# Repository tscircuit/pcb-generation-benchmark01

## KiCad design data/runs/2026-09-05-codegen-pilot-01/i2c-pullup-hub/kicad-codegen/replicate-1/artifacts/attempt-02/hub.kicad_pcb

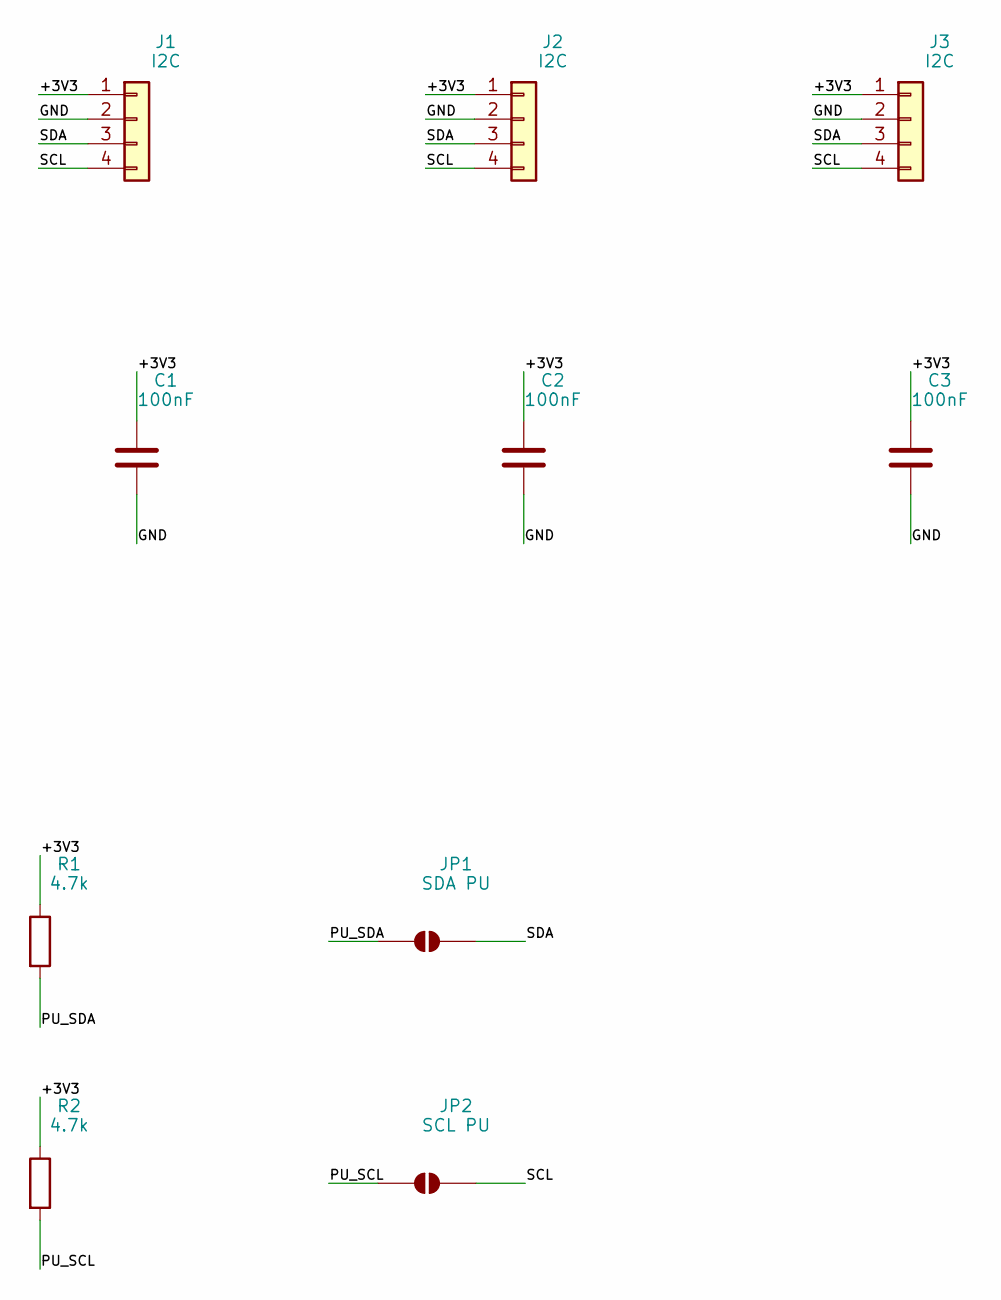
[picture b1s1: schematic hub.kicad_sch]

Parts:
C1, C2, C3: 100nF; C_0805_2012Metric
J1, J2, J3: I2C; PinHeader_1x04_P2.54mm_Vertical
JP1: SDA PU; SolderJumper-2_P1.3mm_Open_Pad1.0x1.5mm
JP2: SCL PU; SolderJumper-2_P1.3mm_Open_Pad1.0x1.5mm
R1, R2: 4.7k; R_0805_2012Metric

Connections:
/+3V3: C1.1, C2.1, C3.1, J1.1, J2.1, J3.1, R1.1, R2.1
/GND: C1.2, C2.2, C3.2, J1.2, J2.2, J3.2
/PU_SCL: JP2.1 (A), R2.2
/PU_SDA: JP1.1 (A), R1.2
/SCL: J1.4, J2.4, J3.4, JP2.2 (B)
/SDA: J1.3, J2.3, J3.3, JP1.2 (B)

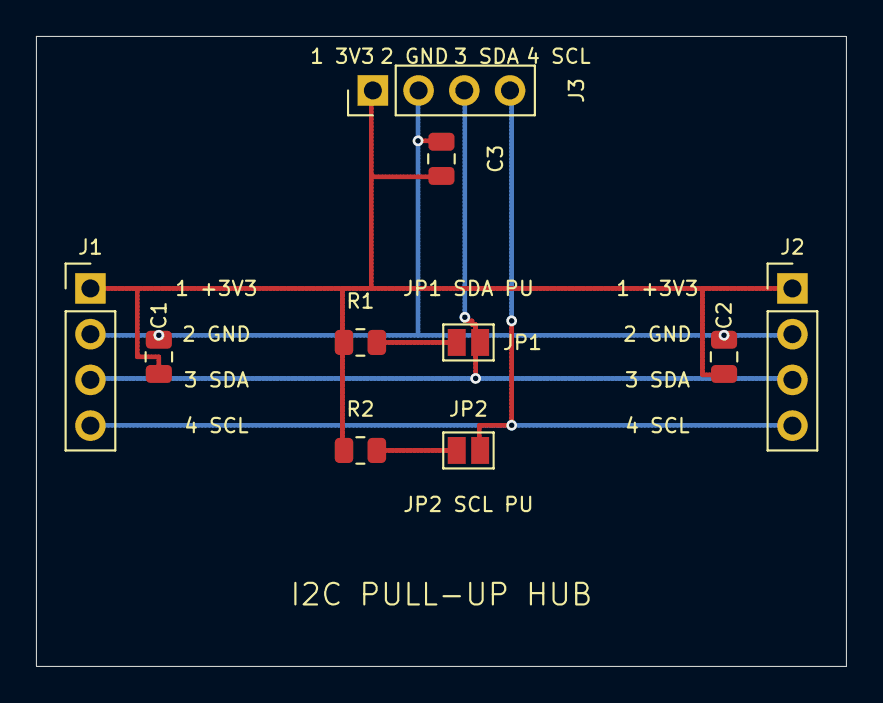
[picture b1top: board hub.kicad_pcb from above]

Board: 2 copper layers, 45.0 x 35.0 mm, 10 parts (0 on the bottom side), 6 nets.

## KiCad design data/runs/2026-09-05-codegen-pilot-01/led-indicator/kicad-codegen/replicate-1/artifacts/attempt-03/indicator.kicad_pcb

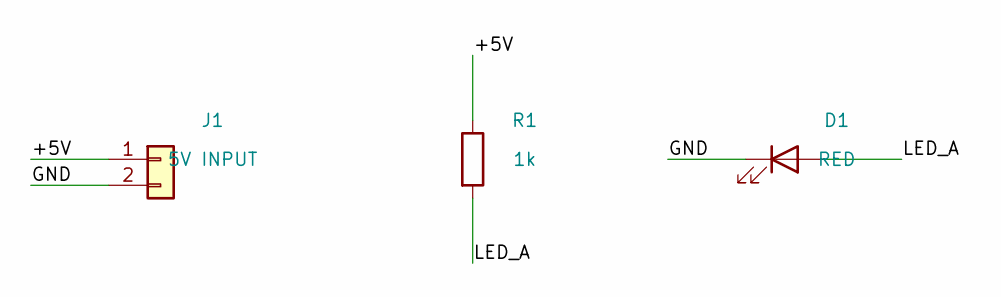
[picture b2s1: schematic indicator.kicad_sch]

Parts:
D1: RED; LED_0805_2012Metric
J1: 5V INPUT; PinHeader_1x02_P2.54mm_Vertical
R1: 1k; R_0805_2012Metric

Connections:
/+5V: J1.1, R1.1
/GND: D1.1 (K), J1.2
/LED_A: D1.2 (A), R1.2

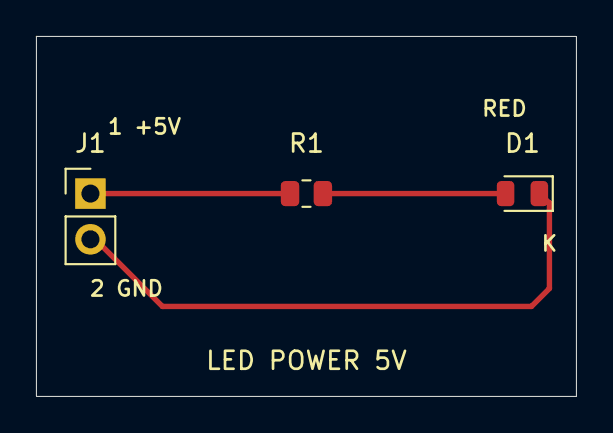
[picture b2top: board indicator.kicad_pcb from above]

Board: 2 copper layers, 30.0 x 20.0 mm, 3 parts (0 on the bottom side), 3 nets.

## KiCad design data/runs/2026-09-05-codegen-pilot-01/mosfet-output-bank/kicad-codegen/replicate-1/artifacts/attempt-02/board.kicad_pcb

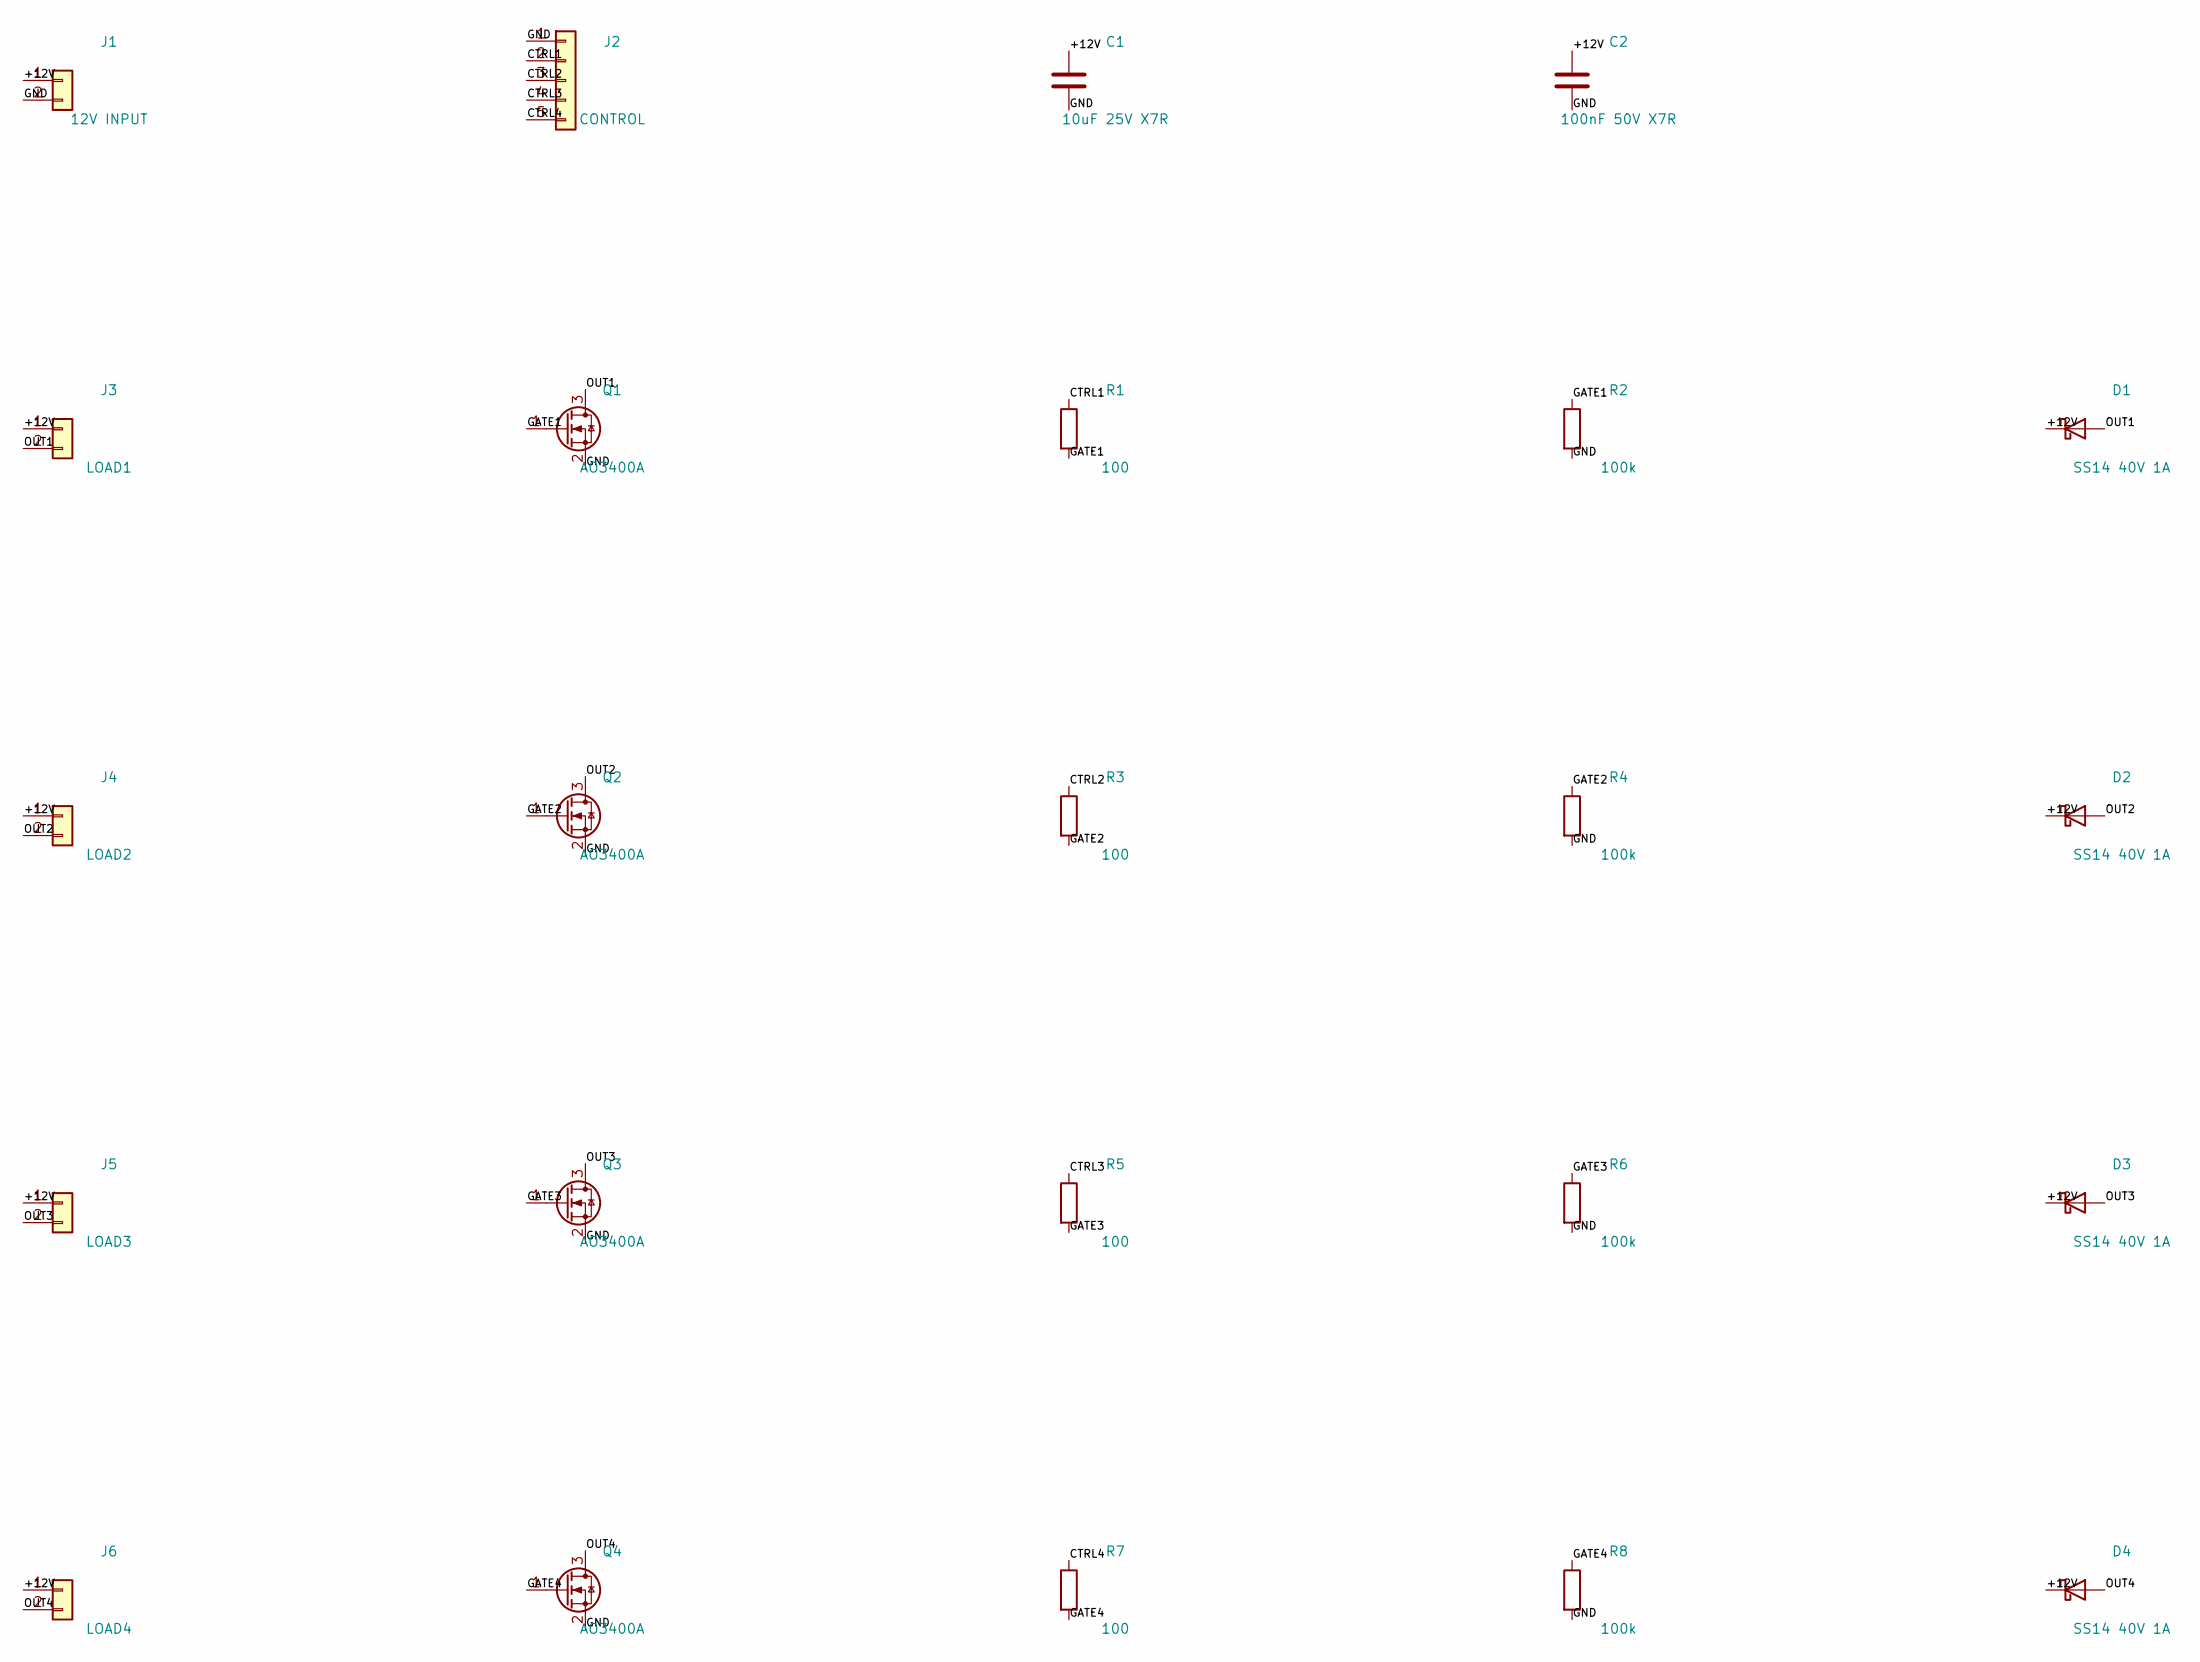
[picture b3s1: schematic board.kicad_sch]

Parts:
C1: 10uF 25V X7R; C_0805_2012Metric
C2: 100nF 50V X7R; C_0805_2012Metric
D1, D2, D3, D4: SS14 40V 1A; D_SMA
J1: 12V INPUT; PinHeader_1x02_P2.54mm_Vertical
J2: CONTROL; PinHeader_1x05_P2.54mm_Vertical
J3: LOAD1; PinHeader_1x02_P2.54mm_Vertical
J4: LOAD2; PinHeader_1x02_P2.54mm_Vertical
J5: LOAD3; PinHeader_1x02_P2.54mm_Vertical
J6: LOAD4; PinHeader_1x02_P2.54mm_Vertical
Q1, Q2, Q3, Q4: AO3400A; SOT-23
R1, R3, R5, R7: 100; R_0805_2012Metric
R2, R4, R6, R8: 100k; R_0805_2012Metric

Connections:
+12V: C1.1, C2.1, D1.1 (K), D2.1 (K), D3.1 (K), D4.1 (K), J1.1, J3.1, J4.1, J5.1, J6.1
CTRL1: J2.2, R1.1
CTRL2: J2.3, R3.1
CTRL3: J2.4, R5.1
CTRL4: J2.5, R7.1
GATE1: Q1.1 (G), R1.2, R2.1
GATE2: Q2.1 (G), R3.2, R4.1
GATE3: Q3.1 (G), R5.2, R6.1
GATE4: Q4.1 (G), R7.2, R8.1
GND: C1.2, C2.2, J1.2, J2.1, Q1.2 (S), Q2.2 (S), Q3.2 (S), Q4.2 (S), R2.2, R4.2, R6.2, R8.2
OUT1: D1.2 (A), J3.2, Q1.3 (D)
OUT2: D2.2 (A), J4.2, Q2.3 (D)
OUT3: D3.2 (A), J5.2, Q3.3 (D)
OUT4: D4.2 (A), J6.2, Q4.3 (D)

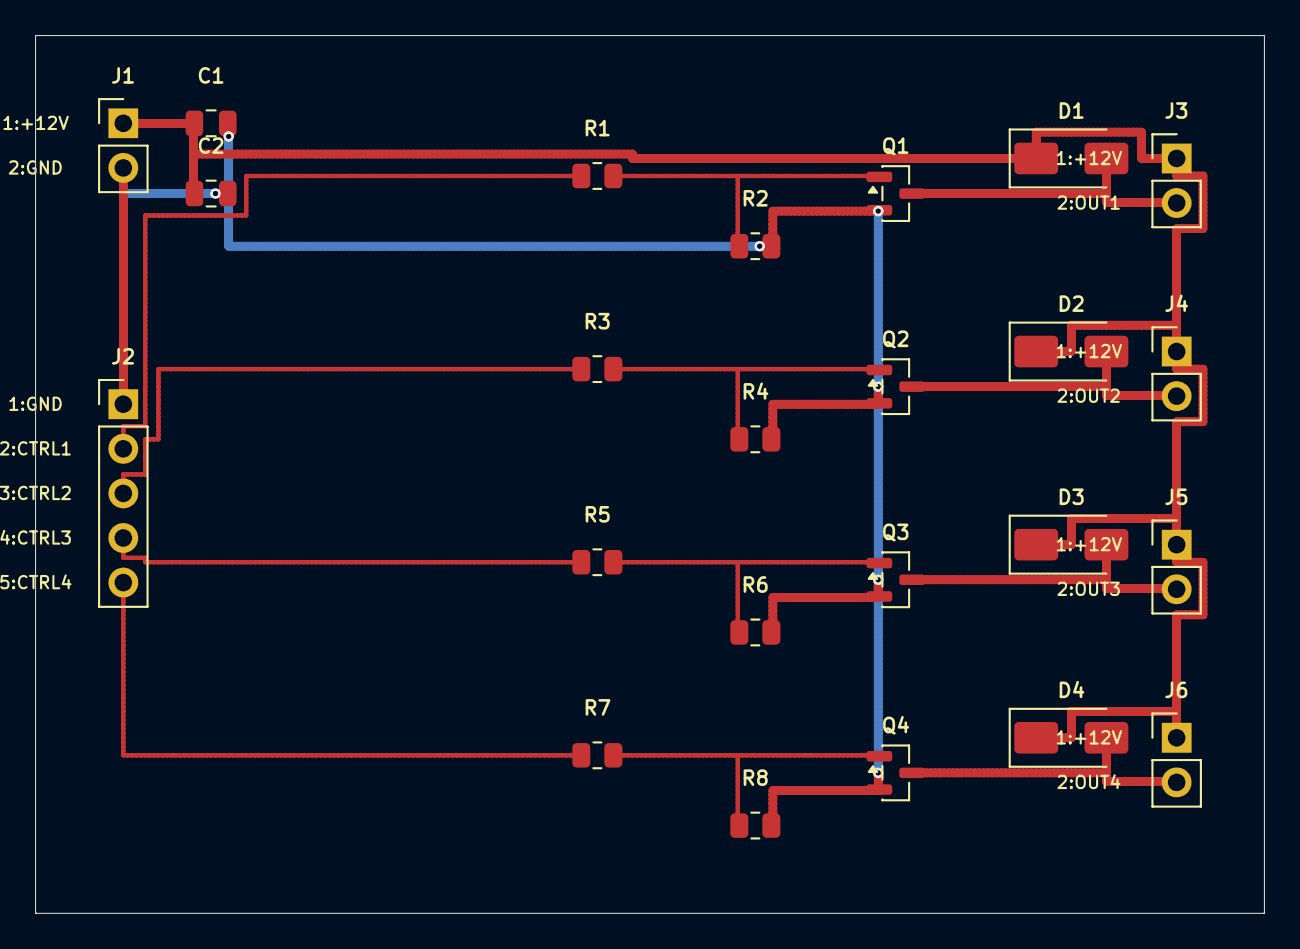
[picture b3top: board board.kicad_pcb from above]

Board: 2 copper layers, 70.0 x 50.0 mm, 24 parts (0 on the bottom side), 14 nets.

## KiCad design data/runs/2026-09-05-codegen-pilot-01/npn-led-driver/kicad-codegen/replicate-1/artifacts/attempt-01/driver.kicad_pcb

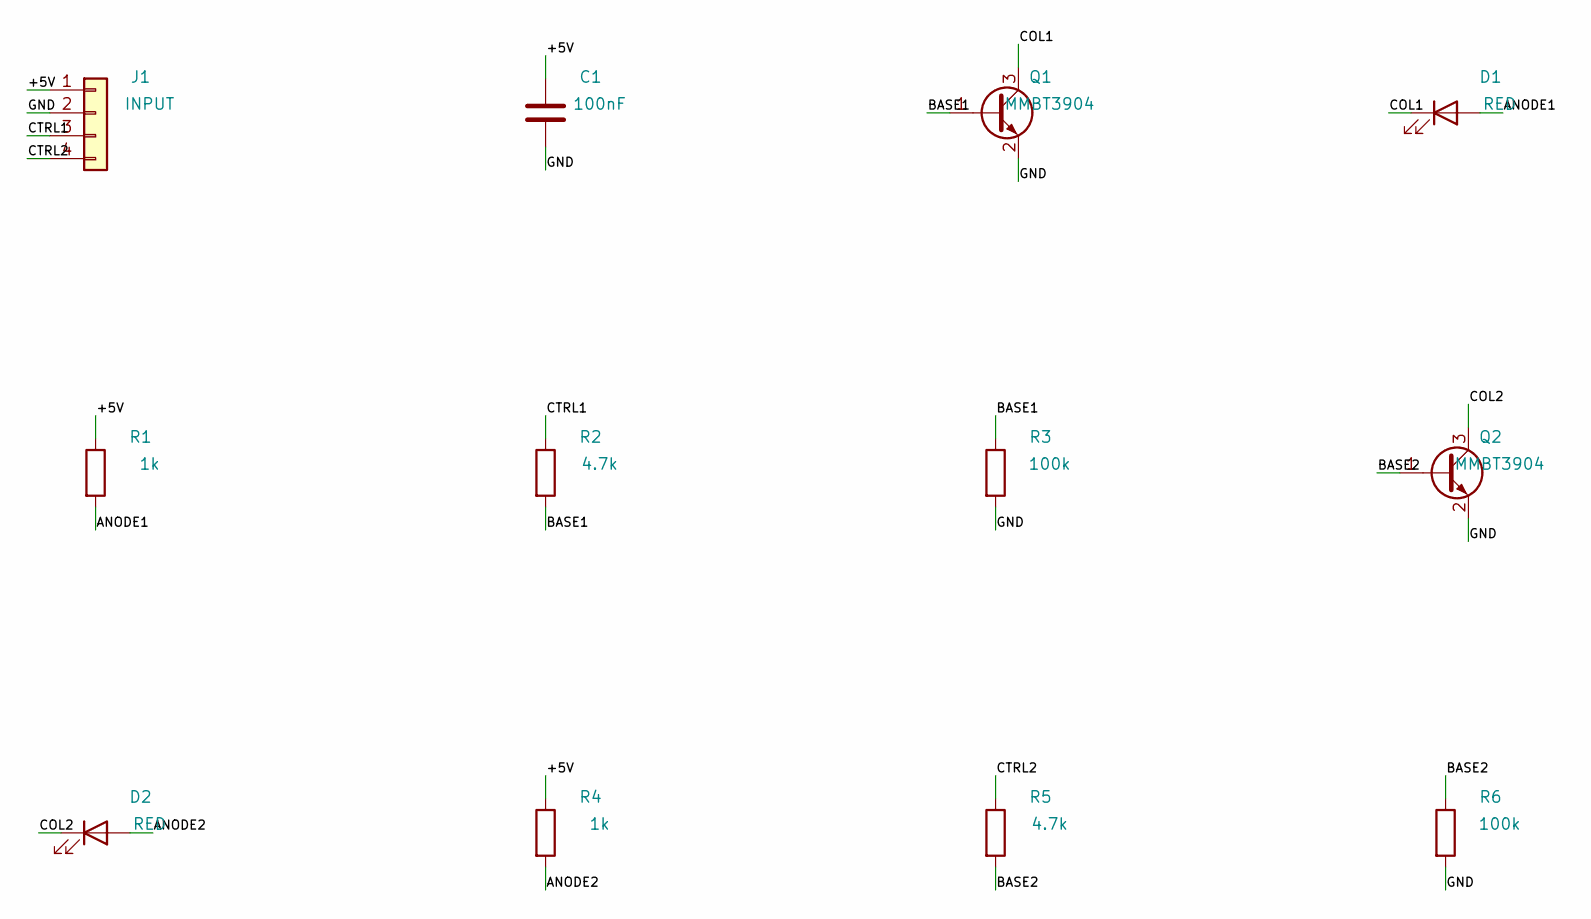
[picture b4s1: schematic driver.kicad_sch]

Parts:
C1: 100nF; C_0805_2012Metric
D1, D2: RED; LED_0805_2012Metric
J1: INPUT; PinHeader_1x04_P2.54mm_Vertical
Q1, Q2: MMBT3904; SOT-23
R1, R4: 1k; R_0805_2012Metric
R2, R5: 4.7k; R_0805_2012Metric
R3, R6: 100k; R_0805_2012Metric

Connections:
+5V: C1.1, J1.1, R1.1, R4.1
ANODE1: D1.2 (A), R1.2
ANODE2: D2.2 (A), R4.2
BASE1: Q1.1 (B), R2.2, R3.1
BASE2: Q2.1 (B), R5.2, R6.1
COL1: D1.1 (K), Q1.3 (C)
COL2: D2.1 (K), Q2.3 (C)
CTRL1: J1.3, R2.1
CTRL2: J1.4, R5.1
GND: C1.2, J1.2, Q1.2 (E), Q2.2 (E), R3.2, R6.2

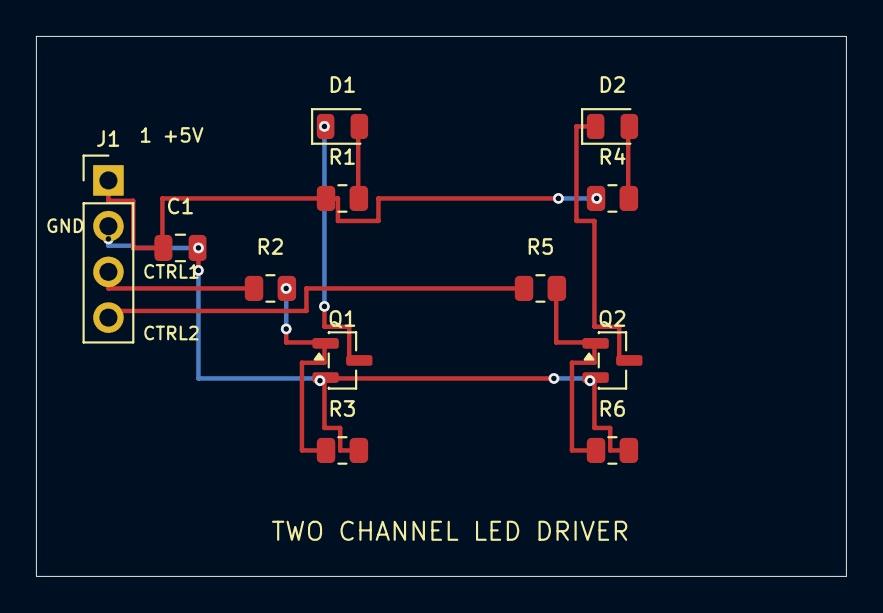
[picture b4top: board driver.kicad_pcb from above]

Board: 2 copper layers, 45.0 x 30.0 mm, 12 parts (0 on the bottom side), 10 nets.

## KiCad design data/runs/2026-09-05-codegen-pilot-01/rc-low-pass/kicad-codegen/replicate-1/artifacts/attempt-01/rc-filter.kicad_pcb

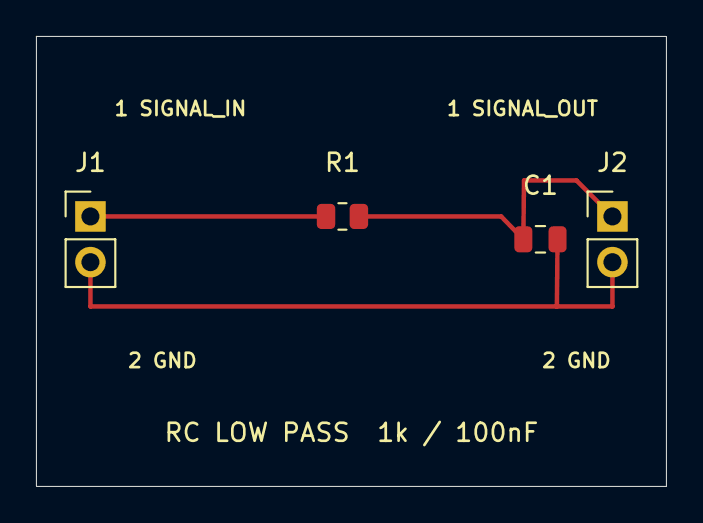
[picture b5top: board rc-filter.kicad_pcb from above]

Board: 2 copper layers, 35.0 x 25.0 mm, 4 parts (0 on the bottom side), 3 nets.

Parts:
C1: 100nF; C_0805_2012Metric
J1: SIGNAL_IN; PinHeader_1x02_P2.54mm_Vertical
J2: SIGNAL_OUT; PinHeader_1x02_P2.54mm_Vertical
R1: 1k; R_0805_2012Metric

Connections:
GND: C1.2, J1.2, J2.2
SIGNAL_IN: J1.1, R1.1
SIGNAL_OUT: C1.1, J2.1, R1.2

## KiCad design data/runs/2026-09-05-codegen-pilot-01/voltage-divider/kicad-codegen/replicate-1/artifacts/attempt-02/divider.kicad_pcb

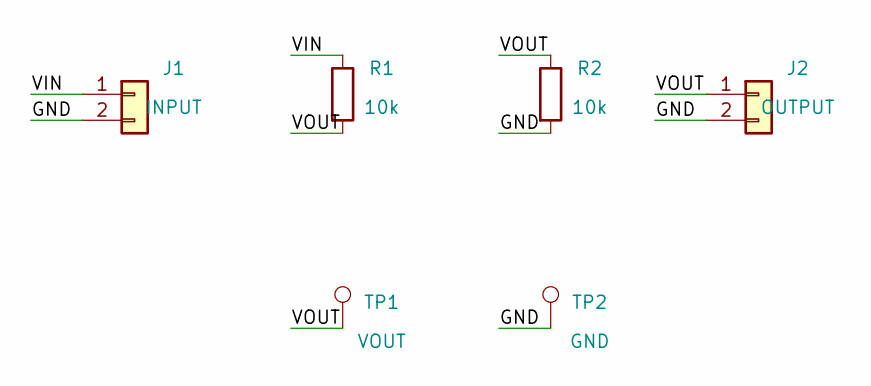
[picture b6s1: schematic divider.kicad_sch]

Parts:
J1: INPUT; PinHeader_1x02_P2.54mm_Vertical
J2: OUTPUT; PinHeader_1x02_P2.54mm_Vertical
R1, R2: 10k; R_0805_2012Metric
TP1: VOUT; TestPoint_Pad_D1.5mm
TP2: GND; TestPoint_Pad_D1.5mm

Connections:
/GND: J1.2, J2.2, R2.2, TP2.1
/VIN: J1.1, R1.1
/VOUT: J2.1, R1.2, R2.1, TP1.1

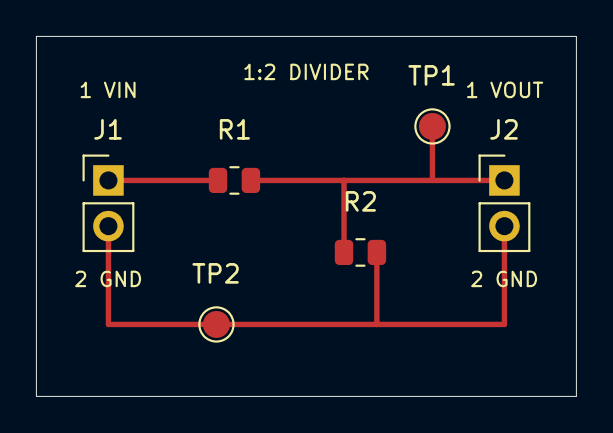
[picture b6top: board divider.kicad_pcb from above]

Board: 2 copper layers, 30.0 x 20.0 mm, 6 parts (0 on the bottom side), 3 nets.

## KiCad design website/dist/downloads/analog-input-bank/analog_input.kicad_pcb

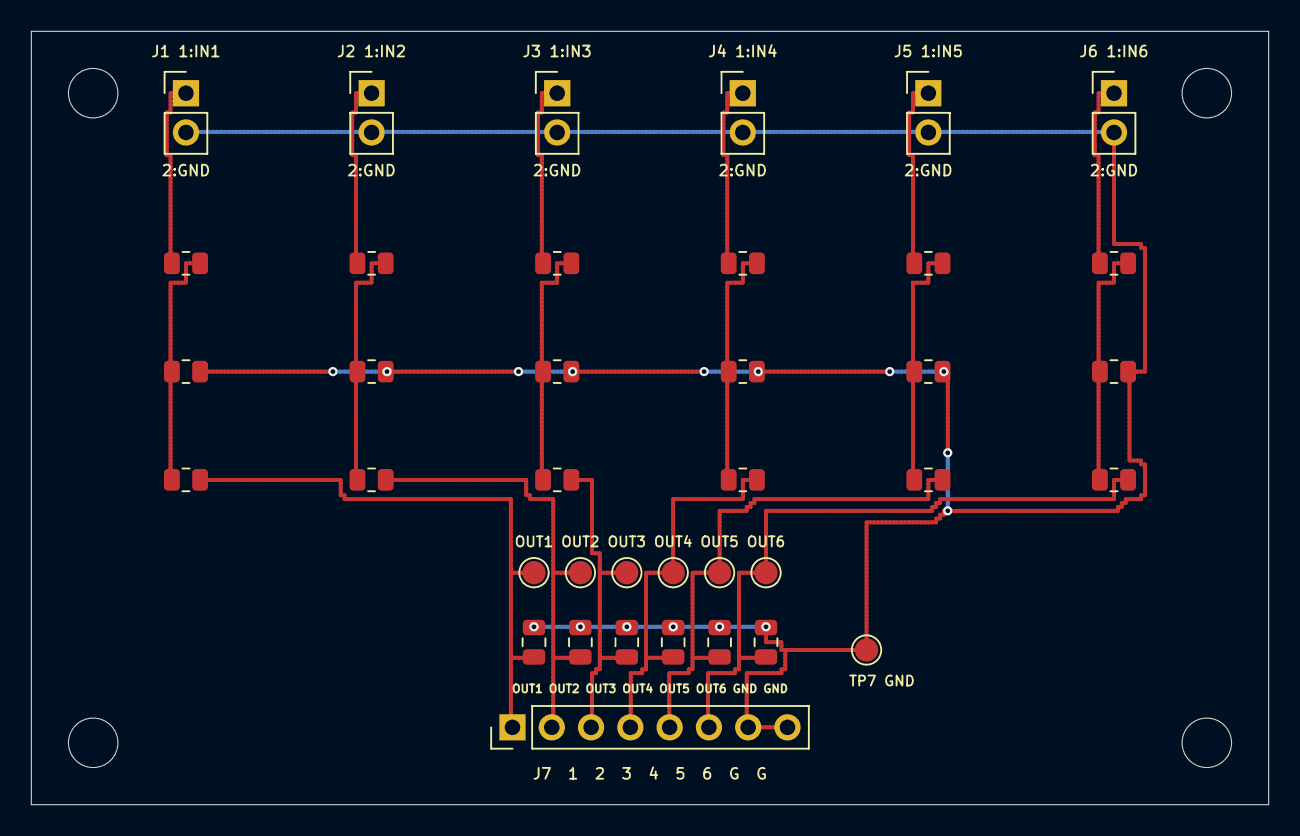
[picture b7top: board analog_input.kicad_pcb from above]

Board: 2 copper layers, 80.0 x 50.0 mm, 42 parts (0 on the bottom side), 19 nets.

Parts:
C1, C2, C3, C4, C5, C6: 100n; C_0805_2012Metric
H1, H2, H3, H4: MountingHole_3.2mm_M3
J1: IN1; PinHeader_1x02_P2.54mm_Vertical
J2: IN2; PinHeader_1x02_P2.54mm_Vertical
J3: IN3; PinHeader_1x02_P2.54mm_Vertical
J4: IN4; PinHeader_1x02_P2.54mm_Vertical
J5: IN5; PinHeader_1x02_P2.54mm_Vertical
J6: IN6; PinHeader_1x02_P2.54mm_Vertical
J7: OUTPUTS; PinHeader_1x08_P2.54mm_Vertical
R1, R4, R7, R10, R13, R16: 10k; R_0805_2012Metric
R2, R5, R8, R11, R14, R17: 20k; R_0805_2012Metric
R3, R6, R9, R12, R15, R18: 1k; R_0805_2012Metric
TP1: OUT1; TestPoint_Pad_D1.5mm
TP2: OUT2; TestPoint_Pad_D1.5mm
TP3: OUT3; TestPoint_Pad_D1.5mm
TP4: OUT4; TestPoint_Pad_D1.5mm
TP5: OUT5; TestPoint_Pad_D1.5mm
TP6: OUT6; TestPoint_Pad_D1.5mm
TP7: GND; TestPoint_Pad_D1.5mm

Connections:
DIV1: R1.2, R2.1, R3.1
DIV2: R4.2, R5.1, R6.1
DIV3: R7.2, R8.1, R9.1
DIV4: R10.2, R11.1, R12.1
DIV5: R13.2, R14.1, R15.1
DIV6: R16.2, R17.1, R18.1
GND: C1.2, C2.2, C3.2, C4.2, C5.2, C6.2, J1.2, J2.2, J3.2, J4.2, J5.2, J6.2, J7.7, J7.8, R2.2, R5.2, R8.2, R11.2, R14.2, R17.2, TP7.1
IN1: J1.1, R1.1
IN2: J2.1, R4.1
IN3: J3.1, R7.1
IN4: J4.1, R10.1
IN5: J5.1, R13.1
IN6: J6.1, R16.1
OUT1: C1.1, J7.1, R3.2, TP1.1
OUT2: C2.1, J7.2, R6.2, TP2.1
OUT3: C3.1, J7.3, R9.2, TP3.1
OUT4: C4.1, J7.4, R12.2, TP4.1
OUT5: C5.1, J7.5, R15.2, TP5.1
OUT6: C6.1, J7.6, R18.2, TP6.1

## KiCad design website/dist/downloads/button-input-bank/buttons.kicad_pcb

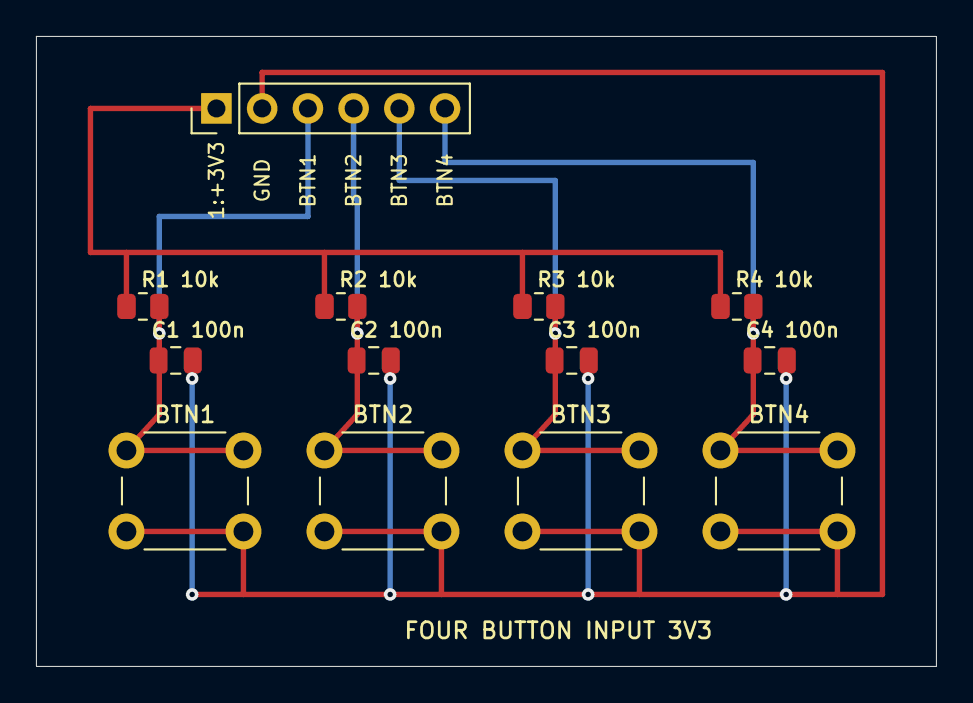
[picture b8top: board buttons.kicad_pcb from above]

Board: 2 copper layers, 50.0 x 35.0 mm, 13 parts (0 on the bottom side), 6 nets.

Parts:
C1, C2, C3, C4: 100nF; C_0805_2012Metric
J1: INPUTS; PinHeader_1x06_P2.54mm_Vertical
R1, R2, R3, R4: 10k; R_0805_2012Metric
SW1: BTN1; SW_PUSH_6mm
SW2: BTN2; SW_PUSH_6mm
SW3: BTN3; SW_PUSH_6mm
SW4: BTN4; SW_PUSH_6mm

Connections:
+3V3: J1.1, R1.1, R2.1, R3.1, R4.1
BTN1: C1.1, J1.3, R1.2, SW1.1
BTN2: C2.1, J1.4, R2.2, SW2.1
BTN3: C3.1, J1.5, R3.2, SW3.1
BTN4: C4.1, J1.6, R4.2, SW4.1
GND: C1.2, C2.2, C3.2, C4.2, J1.2, SW1.2, SW2.2, SW3.2, SW4.2

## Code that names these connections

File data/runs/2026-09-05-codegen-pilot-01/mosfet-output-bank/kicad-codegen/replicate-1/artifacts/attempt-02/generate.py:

import pcbnew as p, os,re,json,uuid,heapq,math,time
from pathlib import Path
HERE=Path(__file__).resolve().parent
LIB=Path('/Users/ankan/Applications/KiCad/KiCad.app/Contents/SharedSupport')
def uid():return str(uuid.uuid4())
def mm(x):return p.FromMM(x)
def pt(x,y):return p.VECTOR2I(mm(x),mm(y))
components=[]
def add(ref,val,lib,fp,nets,x,y):components.append(dict(ref=ref,val=val,lib=lib,fp=fp,nets=nets,x=x,y=y))
add('J1','12V INPUT','Connector_Generic:Conn_01x02','Connector_PinHeader_2.54mm:PinHeader_1x02_P2.54mm_Vertical',['+12V','GND'],15,15)
add('J2','CONTROL','Connector_Generic:Conn_01x05','Connector_PinHeader_2.54mm:PinHeader_1x05_P2.54mm_Vertical',['GND','CTRL1','CTRL2','CTRL3','CTRL4'],15,31)
add('C1','10uF 25V X7R','Device:C','Capacitor_SMD:C_0805_2012Metric',['+12V','GND'],20,15)
add('C2','100nF 50V X7R','Device:C','Capacitor_SMD:C_0805_2012Metric',['+12V','GND'],20,19)
for i,y in enumerate([17,28,39,50],1):
 add('J'+str(i+2),'LOAD'+str(i),'Connector_Generic:Conn_01x02','Connector_PinHeader_2.54mm:PinHeader_1x02_P2.54mm_Vertical',['+12V','OUT'+str(i)],75,y)
 add('Q'+str(i),'AO3400A','Transistor_FET:Q_NMOS_GSD','Package_TO_SOT_SMD:SOT-23',['GATE'+str(i),'GND','OUT'+str(i)],59,y+2)
 add('R'+str(2*i-1),'100','Device:R','Resistor_SMD:R_0805_2012Metric',['CTRL'+str(i),'GATE'+str(i)],42,y+1)
 add('R'+str(2*i),'100k','Device:R','Resistor_SMD:R_0805_2012Metric',['GATE'+str(i),'GND'],51,y+5)
 add('D'+str(i),'SS14 40V 1A','Device:D_Schottky','Diode_SMD:D_SMA',['+12V','OUT'+str(i)],69,y)
# Extract standard symbol definitions without editing library files.
def sex(text):
 tok=re.findall(r'"(?:\\.|[^"\\])*"|[^\s()]+|[()]',text); stack=[]; root=[];cur=root
 for t in tok:
  if t=='(': n=[];cur.append(n);stack.append(cur);cur=n
  elif t==')':cur=stack.pop()
  else:cur.append(t)
 return root[0]
def out(x):return '('+' '.join(out(v) if isinstance(v,list) else v for v in x)+')'
def tag(x,k):return next((v for v in x if isinstance(v,list) and v and v[0]==k),None)
libs={};pins={}
for c in components:
 if c['lib'] in libs:continue
 ln,sn=c['lib'].split(':');tree=sex((LIB/'symbols'/f'{ln}.kicad_sym').read_text());sym=next(x for x in tree if isinstance(x,list) and x[:2]==['symbol','"'+sn+'"']);sym[1]='"'+c['lib']+'"';libs[c['lib']]=out(sym)
 pp=[]
 for child in sym:
  if isinstance(child,list) and child[0]=='symbol':
   for el in child:
    if isinstance(el,list) and el[0]=='pin':pp.append((tag(el,'number')[1].strip('"'),tag(el,'at')[1:]))
 pins[c['lib']]=pp
rootid=uid();s=['(kicad_sch (version 20250114) (generator "pcb-benchmark-codegen") (uuid '+rootid+') (paper "A3") (lib_symbols '+' '.join(libs.values())+')']
for idx,c in enumerate(components):
 # Power/controls top row, each channel separate row.
 if idx<4:x=35+idx*65;y=30
 else:x=35+((idx-4)%5)*65;y=75+((idx-4)//5)*50
 u=uid();c['uuid']=u
 s.append(f'(symbol (lib_id "{c["lib"]}") (at {x} {y} 0) (unit 1) (in_bom yes) (on_board yes) (dnp no) (uuid {u}) (property "Reference" "{c["ref"]}" (at {x+6} {y-5} 0) (effects (font (size 1.27 1.27)))) (property "Value" "{c["val"]}" (at {x+6} {y+5} 0) (effects (font (size 1.27 1.27)))) (property "Footprint" "{c["fp"]}" (at {x} {y} 0) (effects (font (size 1 1)) hide)) (instances (project "board" (path "/{rootid}" (reference "{c["ref"]}") (unit 1)))))')
 for n,a in pins[c['lib']]:
  px=x+float(a[0]);py=y-float(a[1]);net=c['nets'][int(n)-1]
  s.append(f'(label "{net}" (at {px} {py} 0) (effects (font (size 1 1)) (justify left bottom)) (uuid {uid()}))')
s.append(')');(HERE/'board.kicad_sch').write_text('\n'.join(s))
board=p.BOARD();nets={}
for name in sorted({n for c in components for n in c['nets']}):
 net=p.NETINFO_ITEM(board,name);board.Add(net);nets[name]=net
pads=[]
for c in components:
 lib,name=c['fp'].split(':');fp=p.FootprintLoad(str(LIB/'footprints'/f'{lib}.pretty'),name);fp.SetReference(c['ref']);fp.SetValue(c['val']);fp.SetPosition(pt(c['x'],c['y']));fp.SetPath(p.KIID_PATH('/'+rootid+'/'+c['uuid']));board.Add(fp)
 fp.Reference().SetTextSize(pt(.8,.8));fp.Reference().SetPosition(pt(c['x'],c['y']-2.7));fp.Value().SetVisible(False)
 for pad in fp.Pads():
  n=pad.GetNumber()
  if not n:continue
  net=c['nets'][int(n)-1];pad.SetNet(nets[net]);pos=pad.GetPosition();size=pad.GetSize();pads.append(dict(net=net,x=p.ToMM(pos.x),y=p.ToMM(pos.y),sx=p.ToMM(size.x),sy=p.ToMM(size.y),th=pad.GetAttribute()==p.PAD_ATTRIB_PTH))
 for k,n in enumerate(c['nets']):
  if c['ref'].startswith('J'):
   t=p.PCB_TEXT(board);t.SetText(str(k+1)+':'+n);t.SetPosition(pt(c['x']-5,c['y']+k*2.54));t.SetTextSize(pt(.7,.7));t.SetTextThickness(mm(.12));t.SetLayer(p.F_SilkS);board.Add(t)
for a,b in [((10,10),(80,10)),((80,10),(80,60)),((80,60),(10,60)),((10,60),(10,10))]:
 edge=p.PCB_SHAPE();edge.SetShape(p.SHAPE_T_SEGMENT);edge.SetStart(pt(*a));edge.SetEnd(pt(*b));edge.SetLayer(p.Edge_Cuts);edge.SetWidth(mm(.05));board.Add(edge)
# Two-layer grid router, foreign copper clearance 0.27mm. Coordinates relative to absolute mm.
step=.25;N=321;M=241
objects=[(z['net'],z['x'],z['y'],z['sx']/2,z['sy']/2,0) for z in pads]+[(z['net'],z['x'],z['y'],z['sx']/2,z['sy']/2,1) for z in pads if z['th']]
def raster(cx,cy,rx,ry):
 return [(ix,iy) for ix in range(math.ceil((cx-rx)/step),math.floor((cx+rx)/step)+1) for iy in range(math.ceil((cy-ry)/step),math.floor((cy+ry)/step)+1)]
def blocked(net,r):
 b=[set(),set()]
 for name,x,y,rx,ry,l in objects:
  if name!=net:b[l].update(raster(x,y,rx+r+.27,ry+r+.27))
 return b
def line(a,b,net,w,layer):
 if a==b:return
 tr=p.PCB_TRACK(board);tr.SetStart(pt(*a));tr.SetEnd(pt(*b));tr.SetWidth(mm(w));tr.SetLayer(p.F_Cu if layer==0 else p.B_Cu);tr.SetNet(nets[net]);board.Add(tr)
 dist=math.dist(a,b);n=max(1,math.ceil(dist/.12))
 for i in range(n+1):
  x=a[0]+(b[0]-a[0])*i/n;y=a[1]+(b[1]-a[1])*i/n;objects.append((net,x,y,w/2,w/2,layer))
def route(net):
 ps=[z for z in pads if z['net']==net];w=.5 if net in ['GND','+12V'] or net.startswith('OUT') else .25
 conn={(round(ps[0]['x']/step),round(ps[0]['y']/step),0)}
 if ps[0]['th']:conn.add((*next(iter(conn))[:2],1))
 remain=ps[1:]
 while remain:
  z=min(remain,key=lambda z:min(abs(round(z['x']/step)-a)+abs(round(z['y']/step)-b) for a,b,l in conn));remain.remove(z)
  start=(round(z['x']/step),round(z['y']/step),0);b=blocked(net,w/2);vb=blocked(net,.3)
  targetxy=[(a,c) for a,c,l in conn]
  def h(v):return min(abs(v[0]-a)+abs(v[1]-c) for a,c in targetxy)
  heap=[(h(start),0,start)];cost={start:0};prev={};end=None
  while heap:
   _,g,v=heapq.heappop(heap)
   if g!=cost[v]:continue
   if v in conn:end=v;break
   x,y,l=v
   for dx,dy in [(1,0),(-1,0),(0,1),(0,-1)]:
    t=(x+dx,y+dy,l)
    if not (42<=t[0]<=318 and 42<=t[1]<=238) or t[:2] in b[l]:continue
    ng=g+1
    if ng<cost.get(t,1e12):cost[t]=ng;prev[t]=v;heapq.heappush(heap,(ng+h(t),ng,t))
   if (x,y) not in vb[0] and (x,y) not in vb[1]:
    t=(x,y,1-l);ng=g+16
    if ng<cost.get(t,1e12):cost[t]=ng;prev[t]=v;heapq.heappush(heap,(ng+h(t),ng,t))
  if end is None:print('UNROUTED',net,z,flush=True);continue
  path=[end]
  while path[-1]!=start:path.append(prev[path[-1]])
  path.reverse();line((z['x'],z['y']),(start[0]*step,start[1]*step),net,w,0)
  for a,c in zip(path,path[1:]):
   if a[2]==c[2]:line((a[0]*step,a[1]*step),(c[0]*step,c[1]*step),net,w,a[2])
   else:
    via=p.PCB_VIA(board);via.SetPosition(pt(a[0]*step,a[1]*step));via.SetWidth(mm(.6));via.SetDrill(mm(.3));via.SetViaType(p.VIATYPE_THROUGH);via.SetLayerPair(p.F_Cu,p.B_Cu);via.SetNet(nets[net]);board.Add(via)
    for l in [0,1]:objects.append((net,a[0]*step,a[1]*step,.3,.3,l))
  conn.update(path)
  print('ROUTED',net,len(path),flush=True)
 # Connect initial exact pad centre to snapped grid
 a=ps[0];line((a['x'],a['y']),(round(a['x']/step)*step,round(a['y']/step)*step),net,w,0)
for net in sorted(nets,key=lambda n:(0 if n.startswith('GATE') else 1 if n.startswith('OUT') else 2 if n.startswith('CTRL') else 3)):
 route(net)
p.SaveBoard(str(HERE/'board.kicad_pcb'),board)
(HERE/'components.json').write_text(json.dumps(components,indent=2))
(HERE/'board.kicad_pro').write_text(json.dumps({'board':{'design_settings':{'rules':{'min_clearance':.25,'min_track_width':.25},'defaults':{'board_outline_line_width':.05}}}},indent=2))
print('SAVED',flush=True)
